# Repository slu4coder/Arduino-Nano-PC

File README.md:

# Arduino Nano Personal Computer - Squeezing Water from a Stone

I am pushing the limits of how much compute you can get out of an Arduino Nano:

        o 320x200 pixels of monochrome VGA output (optional: 16 row colors)

        o PS/2 keyboard readout

        o requires only 1(!) logic IC 74HC166

# HOW TO USE THE 'NANO HOME COMPUTER'

1. Set the Nano's fuses for output of the 16MHz system clock on pin D8 (see appendix A below).

2. Copy the library files 'os.h' and 'os.S' into a folder '../Arduino/libraries/os'.

3. Start a new sketch with '#include <os.h>'. The following global variables and functions are available:

        int os::frames                                        built-in 16-bit 60Hz frame counter
  
        byte os::vram[25][40]                                 character video RAM array
  
        byte os::cram[25]                                     row color RAM array, available colors are:
  
                                                              WHITE, BLACK, GRAY, RED, GREEN, YELLOW, BLUE, MAGENTA, CYAN,
                                                    
                                                              DKGRAY, DKRED, DKGREEN, DKYELLOW, DKBLUE, DKMAGENTA, DKCYAN.
                                                    
        os::text(String s, byte x, byte y, byte col = 0)      prints text at screen position (x, y), col = 0: don't set row color
  
        os::fill(char c = 32)                                 fills the video RAM with character c
  
        os::scroll()                                          scrolls the video RAM one step upwards
  
        os::wait(int n)                                       waits for n frames
  
        byte os::getkey()                                     returns keystroke ASCII code (none: 0)
  
4. 26KB FLASH (1KB SRAM) of the Nano's 30KB FLASH (2KB SRAM) are usable, respectively.
   To save SRAM, define constant variables in FLASH memory by adding PROGMEM to the data type.
   Constant string arguments can be defined in FLASH by using the F("...") macro.

5. Have fun!

APPENDIX

A. Setting Arduino Nano's fuse bytes via ISP (in-situ programming) for output of system CLK

  o Connect two Arduino Nanos in the following way (programmer -> target):
    D13 -> D13, D12 -> D12, D11 -> D11, D10 -> RESET, 5V -> 5V, GND -> GND
    
  o Arduino IDE: Upload sketch 'examples/ArduinoISP' into programmer and select 'Tools/Programmer/Arduino as ISP'.
  
  o Open the file 'C:\Program Files (x86)\Arduino\hardware\arduino\avr\boards.txt'.
  
  o In section '## Arduino Nano w/ ATmega328P' (line 141), change line 149 'nano.menu.cpu.atmega328.bootloader.low_fuses=0xFF'
    (default) to '...=0xBF' (output system CLK on Pin D8 (B0)) and save the file.
    
  o Close and re-open the Arduino IDE for the changes to become active.
  
  o Select target board: 'Arduino Nano', processor: 'AtMega328P' and 'Tools/Burn bootloader'.

B. Hardware

  Pin A0 (C0):     keyboard input CLK
  
  Pin A1 (C1):     keyboard input DAT
  
  Pin A2-5 (C2-5): 4-bit color output to 74HC08 (optional)
  
  Pin D0-7 (D0-7): 8-bit pixel output to 74HC166
  
  Pin D8 (B0):     CLKO (16MHz system clock output)
  
  Pin D9 (B1):     unused
  
  Pin D10 (B2):    /VSYNC VGA (timer1, every 1/60s)
  
  Pin D11 (B3):    /PE 74166 pixel shift register synchroneous parallel load on rising edge of CP
  
  Pin D12 (B4):    /HSYNC VGA (inside ISR, every 32µs)
  
  Pin D13 (B5):    LED

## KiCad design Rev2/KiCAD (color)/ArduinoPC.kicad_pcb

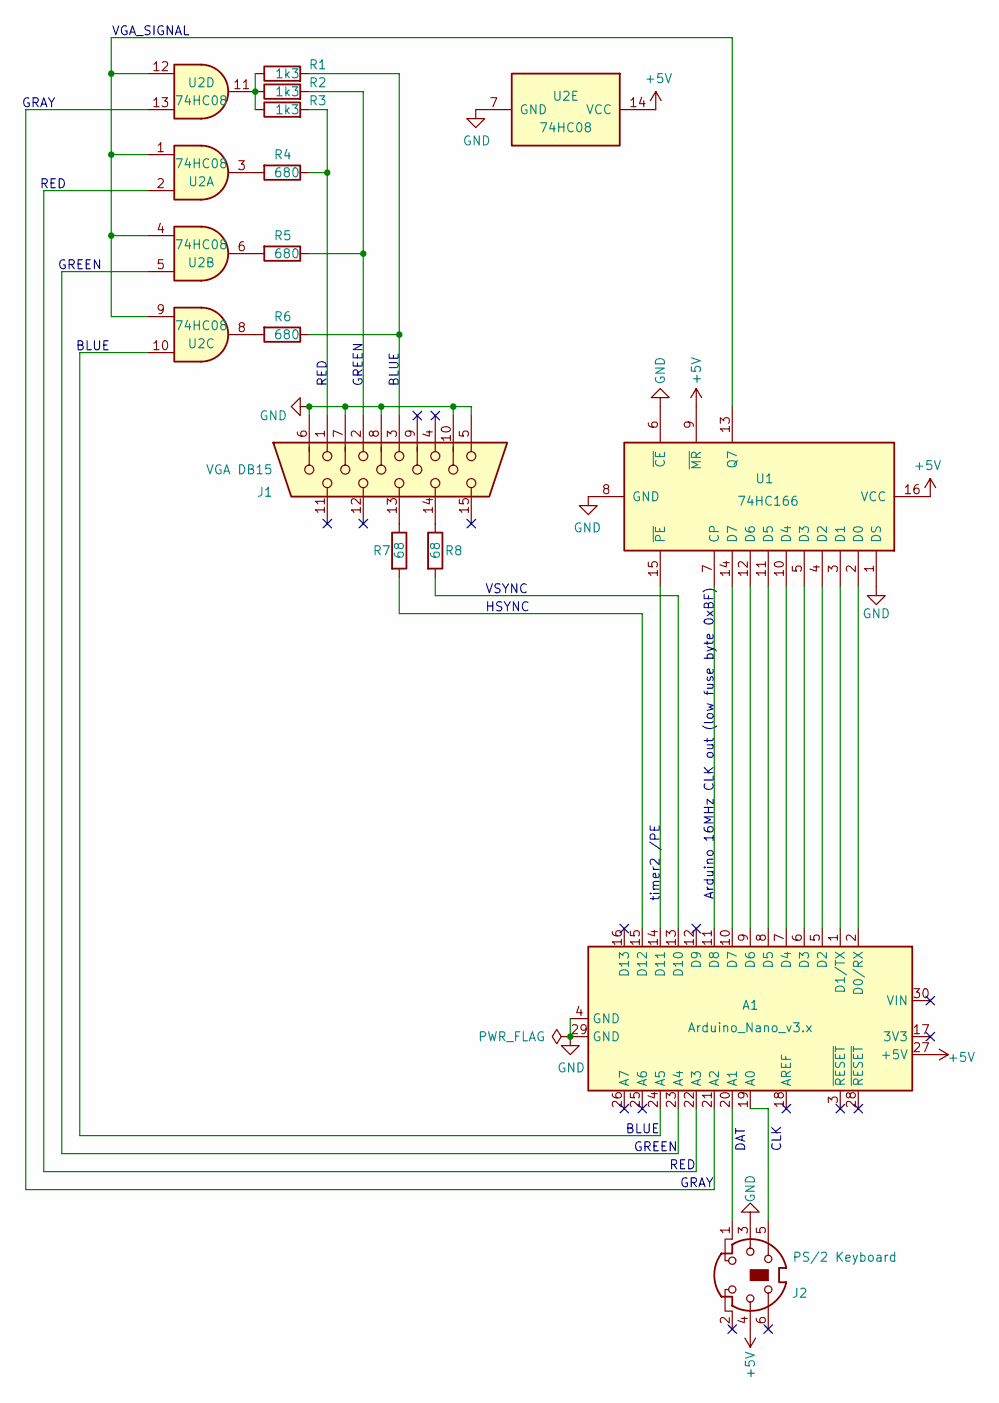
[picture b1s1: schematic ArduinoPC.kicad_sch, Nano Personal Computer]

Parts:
A1: Arduino_Nano_v3.x; Arduino_Nano
J1: VGA DB15; VGA DSUB15HD_female
J2: PS/2 Keyboard; FP_MINI_DIN_6_PS2
R1, R2, R3: 1k3; R_Axial_DIN0207_L6.3mm_D2.5mm_P2.54mm_Vertical
R4, R5, R6: 680; R_Axial_DIN0207_L6.3mm_D2.5mm_P2.54mm_Vertical
R7, R8: 68; R_Axial_DIN0207_L6.3mm_D2.5mm_P2.54mm_Vertical
U1: 74HC166; DIP-16_W7.62mm
U2: 74HC08; DIP-14_W7.62mm

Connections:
+5V: A1.27 (+5V), J2.4, U1.9 (~MR), U1.16 (VCC), U2.14 (VCC)
GND: A1.4 (GND), A1.29 (GND), J1.5, J1.6, J1.7, J1.8, J1.10, J2.3, U1.1 (DS), U1.6 (~CE), U1.8 (GND), U2.7 (GND)
unnamed: A1.1 (D1/TX), U1.3 (D1)
unnamed: A1.2 (D0/RX), U1.2 (D0)
unnamed: A1.5 (D2), U1.4 (D2)
unnamed: A1.6 (D3), U1.5 (D3)
unnamed: A1.7 (D4), U1.10 (D4)
unnamed: A1.8 (D5), U1.11 (D5)
unnamed: A1.9 (D6), U1.12 (D6)
unnamed: A1.10 (D7), U1.14 (D7)
unnamed: A1.11 (D8), U1.7 (CP)
unnamed: A1.13 (D10), R8.2
unnamed: A1.14 (D11), U1.15 (~PE)
unnamed: A1.15 (D12), R7.2
unnamed: A1.19 (A0), J2.5
unnamed: A1.20 (A1), J2.1
unnamed: A1.21 (A2), U2.13
unnamed: A1.22 (A3), U2.2
unnamed: A1.23 (A4), U2.5
unnamed: A1.24 (A5), U2.10
unnamed: J1.1, R3.2, R4.1
unnamed: J1.2, R2.2, R5.1
unnamed: J1.3, R1.2, R6.1
unnamed: J1.13, R7.1
unnamed: J1.14, R8.1
unnamed: R1.1, R2.1, R3.1, U2.11
unnamed: R4.2, U2.3
unnamed: R5.2, U2.6
unnamed: R6.2, U2.8
unnamed: U1.13 (Q7), U2.1, U2.4, U2.9, U2.12

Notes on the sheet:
GREEN
RED
BLUE
VGA_SIGNAL
GRAY
timer2 /PE
Arduino 16MHz CLK out (low fuse byte 0xBF)
CLK
DAT
VSYNC
HSYNC

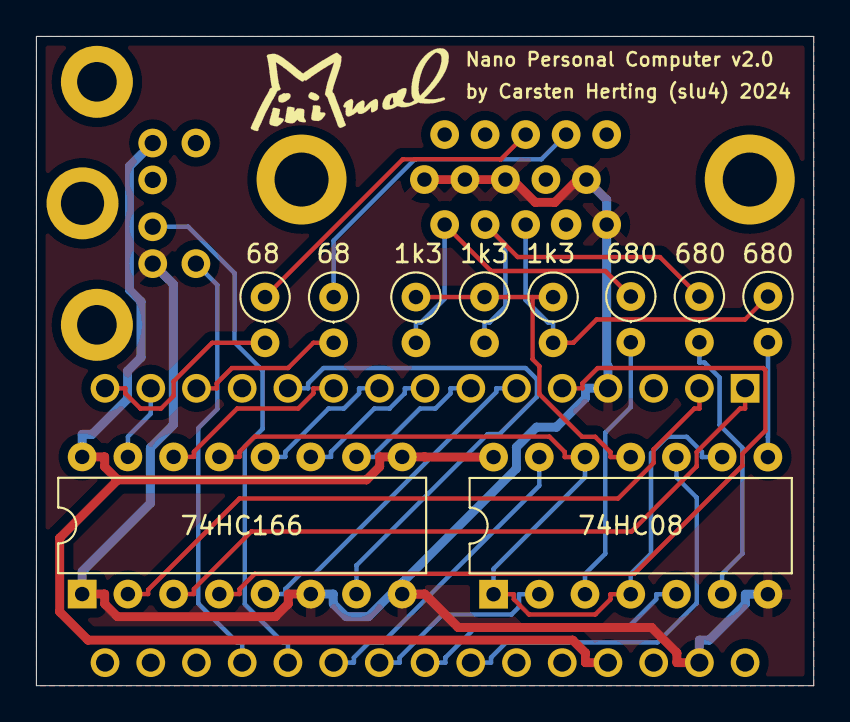
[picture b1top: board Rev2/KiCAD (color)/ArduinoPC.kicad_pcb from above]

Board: 2 copper layers, 43.2 x 36.1 mm, 13 parts (0 on the bottom side), 30 nets.

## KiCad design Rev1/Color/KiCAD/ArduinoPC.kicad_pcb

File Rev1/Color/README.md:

# Arduino Nano Personal Computer 1

16-color mod of my original 'Arduino Nano PC' revision 1 with VGA output and PS/2 keyboard input
running on a single Arduino NANO and 5 additional logic ICs.

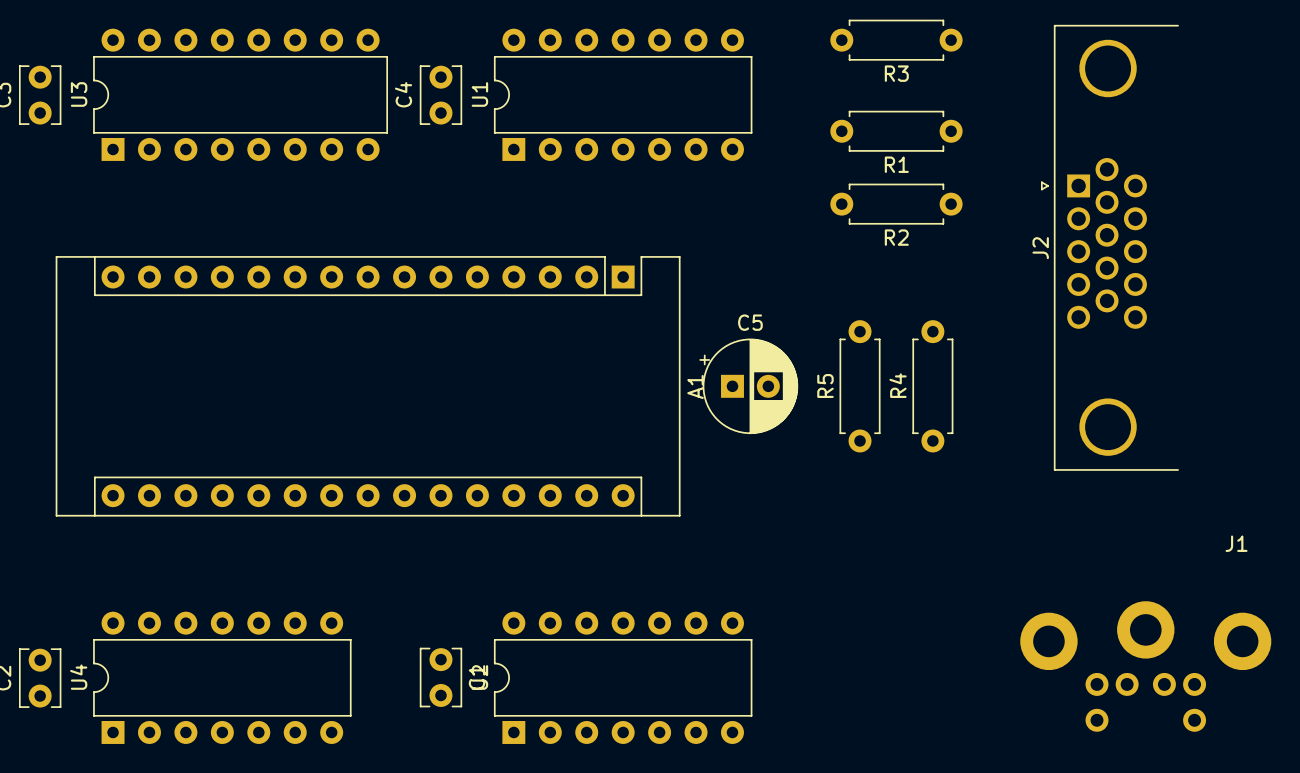
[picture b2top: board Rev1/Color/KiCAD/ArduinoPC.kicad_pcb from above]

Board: 2 copper layers, 17 parts (0 on the bottom side), 33 nets, no tracks yet.

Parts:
A1: Arduino_Nano_v3.x; Arduino_Nano
C1, C2, C3, C4: 100n; C_Disc_D3.8mm_W2.6mm_P2.50mm
C5: 47µ; CP_Radial_D6.3mm_P2.50mm
J1: PS/2 Keyboard; FP_MINI_DIN_6_PS2
J2: VGA DB15 HD Connector (Female); DSUB-15-HD_Female_Horizontal_P2.29x1.98mm_EdgePinOffset3.03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
R1, R2: 68; R_Axial_DIN0207_L6.3mm_D2.5mm_P7.62mm_Horizontal
R3, R4, R5: 220; R_Axial_DIN0207_L6.3mm_D2.5mm_P7.62mm_Horizontal
U1: 74HC86; DIP-14_W7.62mm
U2, U4: 74HC164; DIP-14_W7.62mm
U3: 74HC165; DIP-16_W7.62mm

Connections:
+5V: A1.27, C1.1, C2.2, C3.2, C4.2, C5.1, J1.4, U1.2, U1.5, U1.10, U1.14, U2.2, U2.14, U3.16, U4.2, U4.14
GND: A1.4, A1.29, C1.2, C2.1, C3.1, C4.1, C5.2, J1.3, J2.5, J2.6, J2.7, J2.8, J2.10, U1.7, U2.7, U3.8, U3.10, U3.15, U4.7
unnamed: A1.1, U3.12
unnamed: A1.2, U3.11
unnamed: A1.5, U3.13
unnamed: A1.6, U3.14
unnamed: A1.7, U3.3
unnamed: A1.8, U3.4
unnamed: A1.9, R5.2, U3.5
unnamed: A1.10, R4.2, U3.6
unnamed: A1.11, U3.2
unnamed: A1.12, U2.9, U4.9
unnamed: A1.13, R2.2
unnamed: A1.14, U1.1, U1.13
unnamed: A1.15, R1.2
unnamed: A1.19, U4.4
unnamed: A1.20, U4.3
unnamed: A1.21, U2.13, U4.1
unnamed: A1.22, U2.12
unnamed: A1.23, U2.11
unnamed: A1.24, U2.10
unnamed: J1.1, U2.1
unnamed: J1.5, U2.8, U4.8
unnamed: J2.1, J2.2, J2.3, R3.1
unnamed: J2.13, R1.1
unnamed: J2.14, R2.1
unnamed: R3.2, U3.9
unnamed: R4.1, U2.5
unnamed: R5.1, U2.6
unnamed: U1.3, U1.4
unnamed: U1.6, U1.9
unnamed: U1.11, U3.1
unnamed: U1.8, U1.12

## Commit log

2020-09-22 Initial release
2020-10-20 minor optimizations in some resistor values
2020-10-20 minor cosmetic updates
2021-03-25 Upgrade 1.1
2021-03-25 Upgrade Version 1.1
2021-03-25 Upgrade Version 1,1
2021-03-26 Upgrade to version 1.1
2021-04-16 Fixing jitter compensation on some monitors
2023-07-18 Restructuring

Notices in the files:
Rev2/KiCAD (color)/ArduinoPC.kicad_sch:
creativecommons.org/licenses/by-nc-sa/3.0/deed.en
License: CC BY-NC-SA 3.0
